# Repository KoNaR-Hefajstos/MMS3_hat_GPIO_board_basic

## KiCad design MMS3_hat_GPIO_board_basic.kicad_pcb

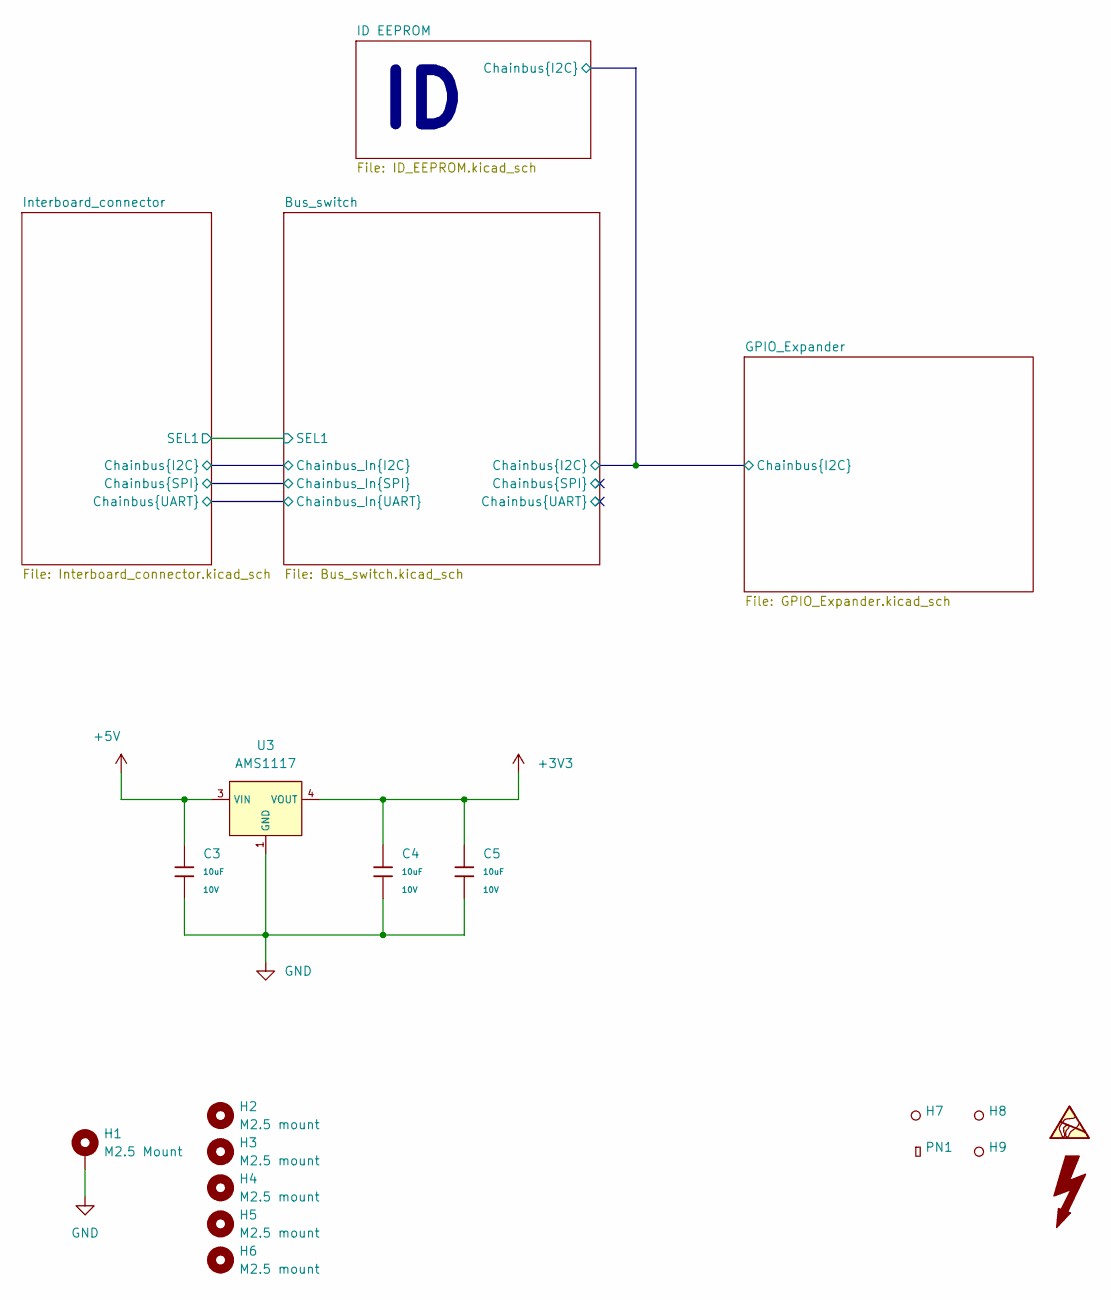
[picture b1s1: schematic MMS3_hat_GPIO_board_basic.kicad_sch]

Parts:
C3, C4, C5: 10uF; C_0603; Voltage Rated 10V; Tolerance ±10%; Part CL10A106KP8NNNC; LCSC C19702
H1: M2.5 Mount; MountingHole_2.7mm_M2.5_DIN965_Pad_TopOnly
H2, H3, H4, H5, H6: M2.5 mount; MountingHole_2.7mm_M2.5
H7, H8, H9: Hole_Tooling_JLCPCB
PN1: Part_Num_JLCPCB
U3: AMS1117; SOT-223-3_L6.5-W3.4-P2.30-LS7.0-BR; Output Voltage 3.3V; Dropout Voltage 1.3V@(800mA); Part AMS1117-3.3; LCSC C6186

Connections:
+3V3: C4.1, C5.1, U3.2 (VOUT), U3.4 (VOUT); also elsewhere on the board
+5V: C3.1, U3.3 (VIN); also elsewhere on the board
GND: C3.2, C4.2, C5.2, H1.1 (1_1), U3.1 (GND); also elsewhere on the board

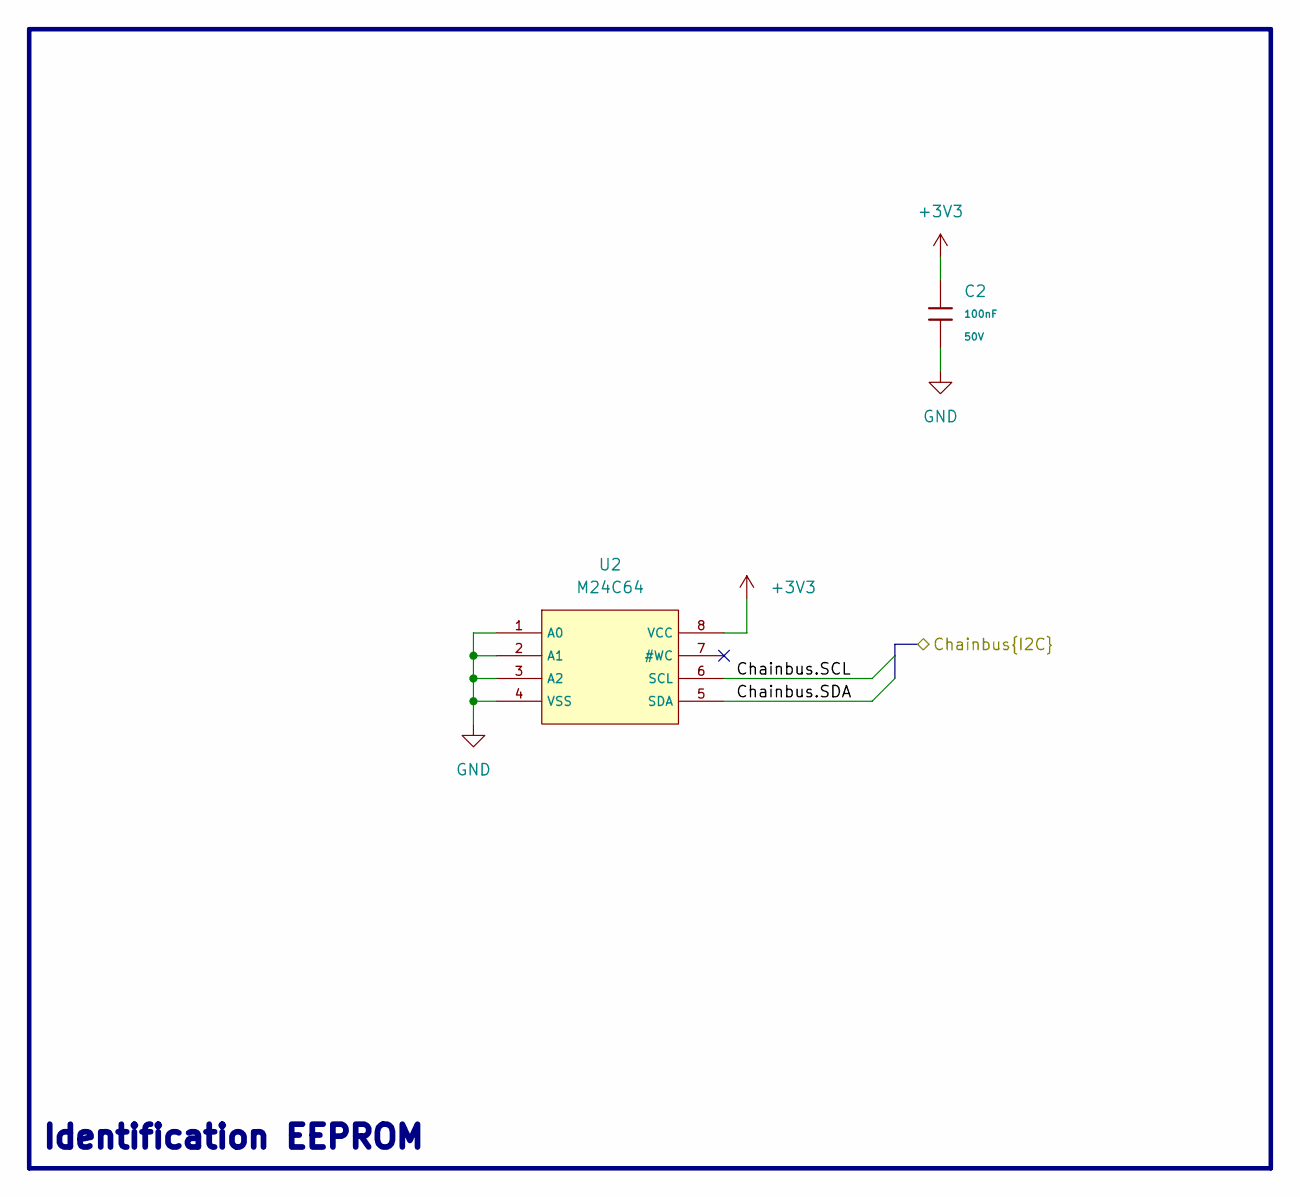
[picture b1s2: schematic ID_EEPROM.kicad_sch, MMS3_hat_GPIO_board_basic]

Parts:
C2: 100nF; C_0603; Voltage Rated 50V; Tolerance ±10%; Part CC0603KRX7R9BB104; LCSC C14663
U2: M24C64; SOIC-8_L5.0-W4.0-P1.27-LS6.0-BL; Supply Voltage 1.8V~5.5V; Part M24C64-RMN6TP; LCSC C79988

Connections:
+3V3: C2.1, U2.8 (VCC); also elsewhere on the board
/Bus_switch/Chainbus.SCL: U2.6 (SCL); also elsewhere on the board
/Bus_switch/Chainbus.SDA: U2.5 (SDA); also elsewhere on the board
GND: C2.2, U2.1 (A0), U2.2 (A1), U2.3 (A2), U2.4 (VSS); also elsewhere on the board

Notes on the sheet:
Identification EEPROM

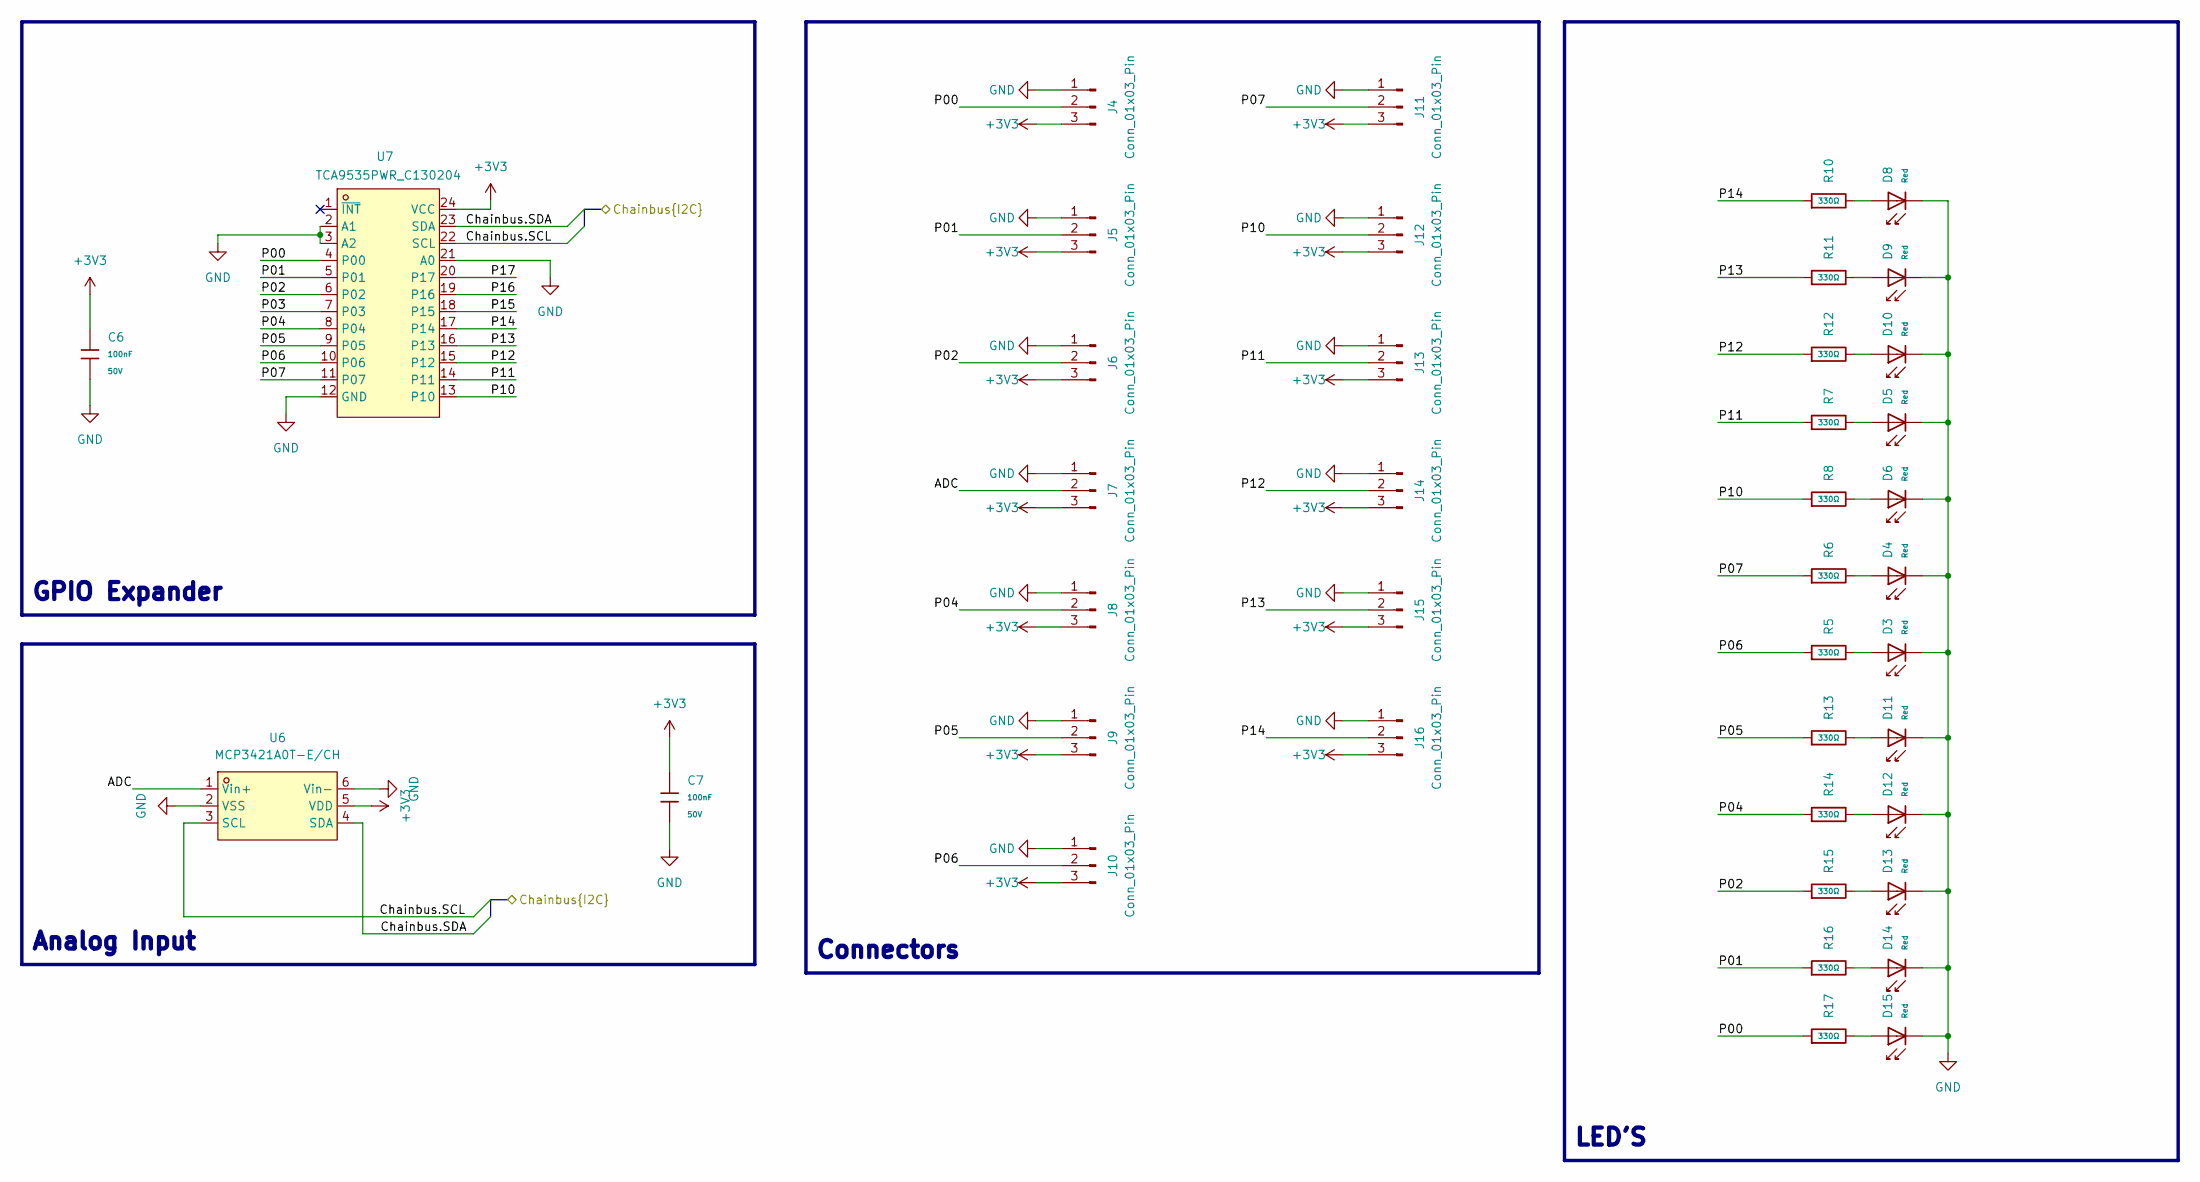
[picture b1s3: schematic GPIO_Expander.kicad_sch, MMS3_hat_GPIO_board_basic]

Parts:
C6, C7: 100nF; C_0603; Voltage Rated 50V; Tolerance ±10%; Part CC0603KRX7R9BB104; LCSC C14663
D3, D4, D5, D6, D8, D9, D10, D11, D12, D13, D14, D15: Red; D_0603; Part KT-0603R; LCSC C2286
J4, J5, J6, J7, J8, J9, J10, J11, J12, J13, J14, J15, J16: Conn_01x03_Pin; JST_XH_S3B-XH-A_1x03_P2.50mm_Horizontal
R5, R6, R7, R8, R10, R11, R12, R13, R14, R15, R16, R17: 330Ω; R_0402; Overload Voltage (Max) 50V; Tolerance ±1%; Part 0402WGF3300TCE; LCSC C25104
U6: MCP3421A0T-E/CH; SOT-23-6_L2.9-W1.6-P0.95-LS2.8-BR; MPN MCP3421A0T-E/CH; LCSC Part C29454
U7: TCA9535PWR_C130204; TSSOP-24_L7.8-W4.4-P0.65-LS6.4-BL; MPN TCA9535PWR; LCSC Part C130204

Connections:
+3V3: C6.1, C7.1, J4.3, J5.3, J6.3, J7.3, J8.3, J9.3, J10.3, J11.3, J12.3, J13.3, J14.3, J15.3, J16.3, U6.5 (VDD), U7.24 (VCC); also elsewhere on the board
/Bus_switch/Chainbus.SCL: U6.3 (SCL), U7.22 (SCL); also elsewhere on the board
/Bus_switch/Chainbus.SDA: U6.4 (SDA), U7.23 (SDA); also elsewhere on the board
/GPIO_Expander/ADC: J7.2, U6.1 (Vin+)
/GPIO_Expander/P00: J4.2, R17.1, U7.4 (P00)
/GPIO_Expander/P01: J5.2, R16.1, U7.5 (P01)
/GPIO_Expander/P02: J6.2, R15.1, U7.6 (P02)
/GPIO_Expander/P03: U7.7 (P03)
/GPIO_Expander/P04: J8.2, R14.1, U7.8 (P04)
/GPIO_Expander/P05: J9.2, R13.1, U7.9 (P05)
/GPIO_Expander/P06: J10.2, R5.1, U7.10 (P06)
/GPIO_Expander/P07: J11.2, R6.1, U7.11 (P07)
/GPIO_Expander/P10: J12.2, R8.1, U7.13 (P10)
/GPIO_Expander/P11: J13.2, R7.1, U7.14 (P11)
/GPIO_Expander/P12: J14.2, R12.1, U7.15 (P12)
/GPIO_Expander/P13: J15.2, R11.1, U7.16 (P13)
/GPIO_Expander/P14: J16.2, R10.1, U7.17 (P14)
/GPIO_Expander/P15: U7.18 (P15)
/GPIO_Expander/P16: U7.19 (P16)
/GPIO_Expander/P17: U7.20 (P17)
GND: C6.2, C7.2, D3.1, D4.1, D5.1, D6.1, D8.1, D9.1, D10.1, D11.1, D12.1, D13.1, D14.1, D15.1, J4.1, J5.1, J6.1, J7.1, J8.1, J9.1, J10.1, J11.1, J12.1, J13.1, J14.1, J15.1, J16.1, U6.2 (VSS), U6.6 (Vin-), U7.2 (A1), U7.3 (A2), U7.12 (GND), U7.21 (A0); also elsewhere on the board
unnamed: D3.2, R5.2
unnamed: D4.2, R6.2
unnamed: D5.2, R7.2
unnamed: D6.2, R8.2
unnamed: D8.2, R10.2
unnamed: D9.2, R11.2
unnamed: D10.2, R12.2
unnamed: D11.2, R13.2
unnamed: D12.2, R14.2
unnamed: D13.2, R15.2
unnamed: D14.2, R16.2
unnamed: D15.2, R17.2

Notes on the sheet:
GPIO Expander
LED'S
Connectors
Analog Input

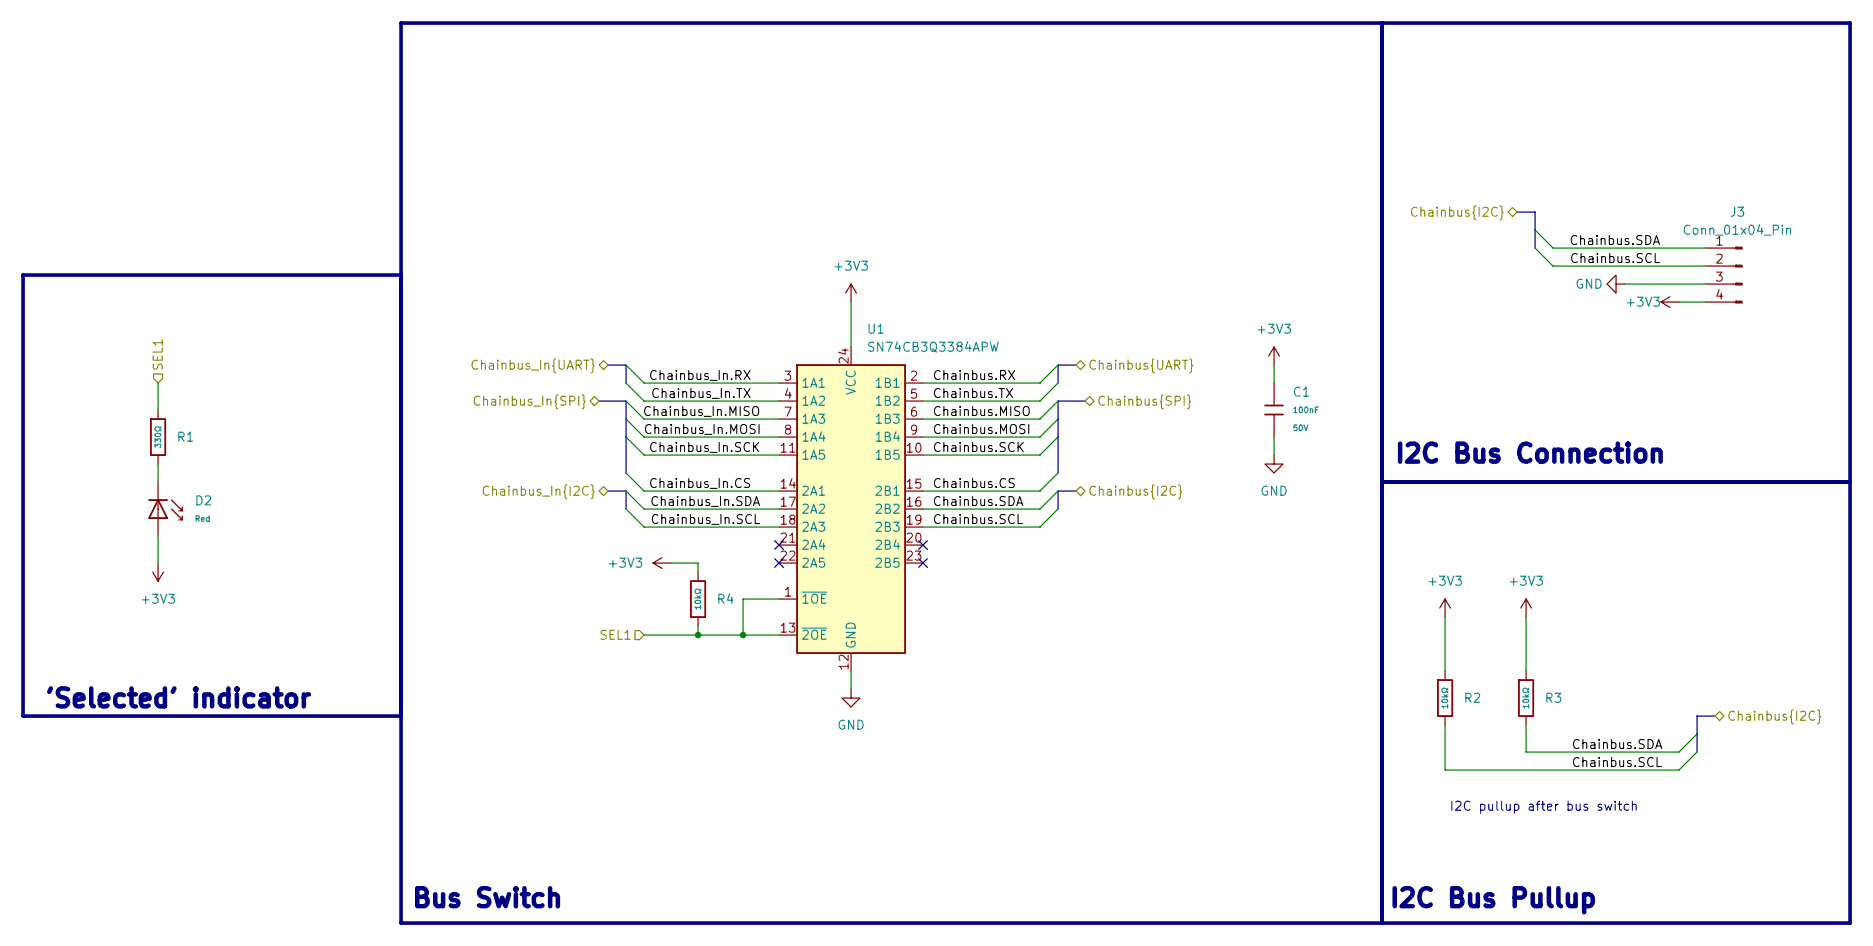
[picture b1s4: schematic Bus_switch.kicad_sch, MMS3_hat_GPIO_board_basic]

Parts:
C1: 100nF; C_0603; Voltage Rated 50V; Tolerance ±10%; Part CC0603KRX7R9BB104; LCSC C14663
D2: Red; D_0603; Part KT-0603R; LCSC C2286
J3: Conn_01x04_Pin; PinHeader_1x04_P2.54mm_Vertical
R1: 330Ω; R_0402; Overload Voltage (Max) 50V; Tolerance ±1%; Part 0402WGF3300TCE; LCSC C25104
R2, R3, R4: 10kΩ; R_0402; Overload Voltage (Max) 50V; Tolerance ±1%; Part 0402WGF1002TCE; LCSC C25744
U1: SN74CB3Q3384APW; TSSOP-24_4.4x7.8mm_P0.65mm; LCSC C469874

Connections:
+3V3: C1.1, D2.2, J3.4, R2.1, R3.1, R4.2, U1.24 (VCC); also elsewhere on the board
/Bus_switch/Chainbus.CS: U1.15 (2B1)
/Bus_switch/Chainbus.MISO: U1.6 (1B3)
/Bus_switch/Chainbus.MOSI: U1.9 (1B4)
/Bus_switch/Chainbus.RX: U1.2 (1B1)
/Bus_switch/Chainbus.SCK: U1.10 (1B5)
/Bus_switch/Chainbus.SCL: J3.2, R2.2, U1.19 (2B3); also elsewhere on the board
/Bus_switch/Chainbus.SDA: J3.1, R3.2, U1.16 (2B2); also elsewhere on the board
/Bus_switch/Chainbus.TX: U1.5 (1B2)
/Bus_switch/Chainbus_In.CS: U1.14 (2A1); also elsewhere on the board
/Bus_switch/Chainbus_In.MISO: U1.7 (1A3); also elsewhere on the board
/Bus_switch/Chainbus_In.MOSI: U1.8 (1A4); also elsewhere on the board
/Bus_switch/Chainbus_In.RX: U1.3 (1A1); also elsewhere on the board
/Bus_switch/Chainbus_In.SCK: U1.11 (1A5); also elsewhere on the board
/Bus_switch/Chainbus_In.SCL: U1.18 (2A3); also elsewhere on the board
/Bus_switch/Chainbus_In.SDA: U1.17 (2A2); also elsewhere on the board
/Bus_switch/Chainbus_In.TX: U1.4 (1A2); also elsewhere on the board
/Bus_switch/SEL1: R1.1, R4.1, U1.1 (~1OE), U1.13 (~2OE); also elsewhere on the board
GND: C1.2, J3.3, U1.12 (GND); also elsewhere on the board
unnamed: D2.1, R1.2

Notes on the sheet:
Bus Switch
'Selected' indicator
I2C Bus Pullup
I2C pullup after bus switch
I2C Bus Connection

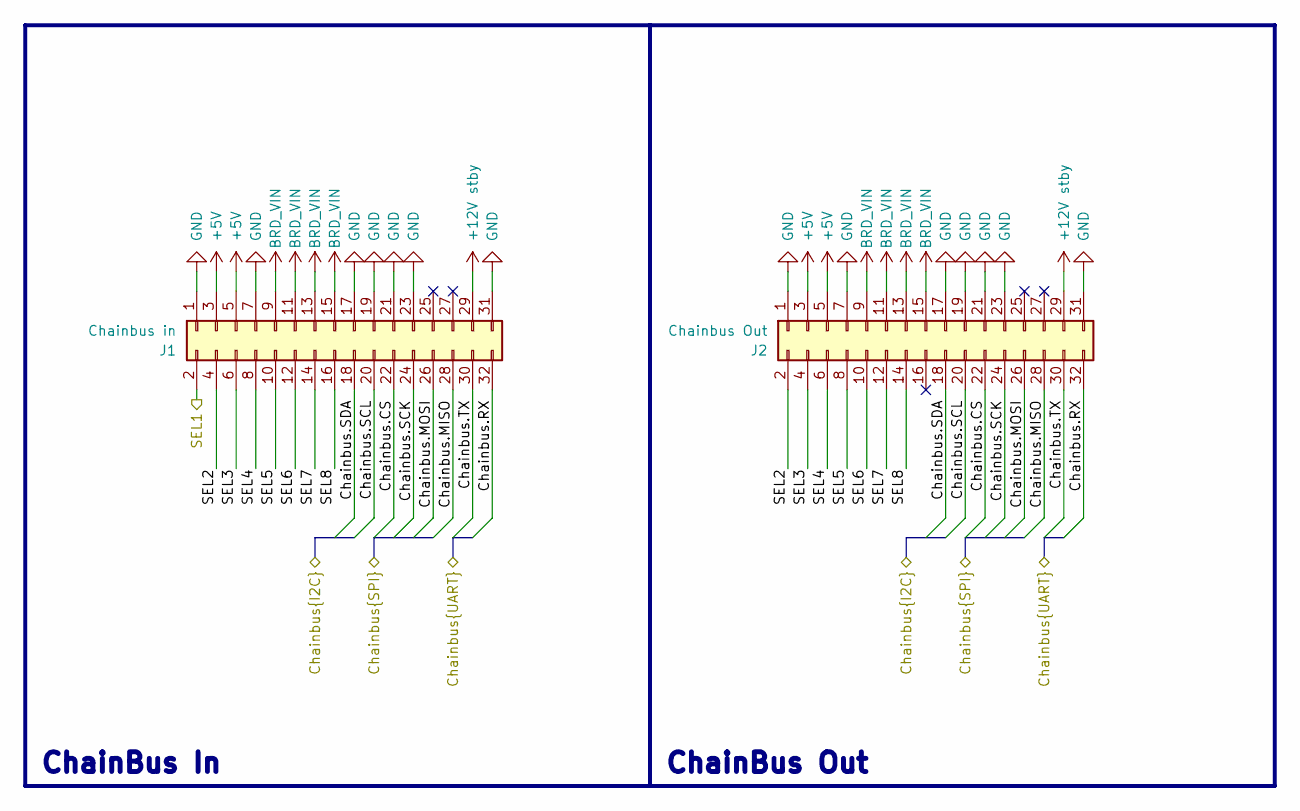
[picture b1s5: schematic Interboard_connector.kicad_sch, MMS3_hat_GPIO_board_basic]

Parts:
J1: Chainbus in; PinHeader_2x16_P2.54mm_Vertical_SMD
J2: Chainbus Out; PinSocket_2x16_P2.54mm_Vertical_SMD

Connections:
+5V: J1.3, J1.5, J2.3, J2.5; also elsewhere on the board
+12V stby: J1.29, J2.29
/Bus_switch/Chainbus_In.CS: J1.22, J2.22; also elsewhere on the board
/Bus_switch/Chainbus_In.MISO: J1.28, J2.28; also elsewhere on the board
/Bus_switch/Chainbus_In.MOSI: J1.26, J2.26; also elsewhere on the board
/Bus_switch/Chainbus_In.RX: J1.32, J2.32; also elsewhere on the board
/Bus_switch/Chainbus_In.SCK: J1.24, J2.24; also elsewhere on the board
/Bus_switch/Chainbus_In.SCL: J1.20, J2.20; also elsewhere on the board
/Bus_switch/Chainbus_In.SDA: J1.18, J2.18; also elsewhere on the board
/Bus_switch/Chainbus_In.TX: J1.30, J2.30; also elsewhere on the board
/Bus_switch/SEL1: J1.2; also elsewhere on the board
/Interboard_connector/SEL2: J1.4, J2.2
/Interboard_connector/SEL3: J1.6, J2.4
/Interboard_connector/SEL4: J1.8, J2.6
/Interboard_connector/SEL5: J1.10, J2.8
/Interboard_connector/SEL6: J1.12, J2.10
/Interboard_connector/SEL7: J1.14, J2.12
/Interboard_connector/SEL8: J1.16, J2.14
BRD_VIN: J1.9, J1.11, J1.13, J1.15, J2.9, J2.11, J2.13, J2.15
GND: J1.1, J1.7, J1.17, J1.19, J1.21, J1.23, J1.31, J2.1, J2.7, J2.17, J2.19, J2.21, J2.23, J2.31; also elsewhere on the board

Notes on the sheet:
ChainBus In
ChainBus Out

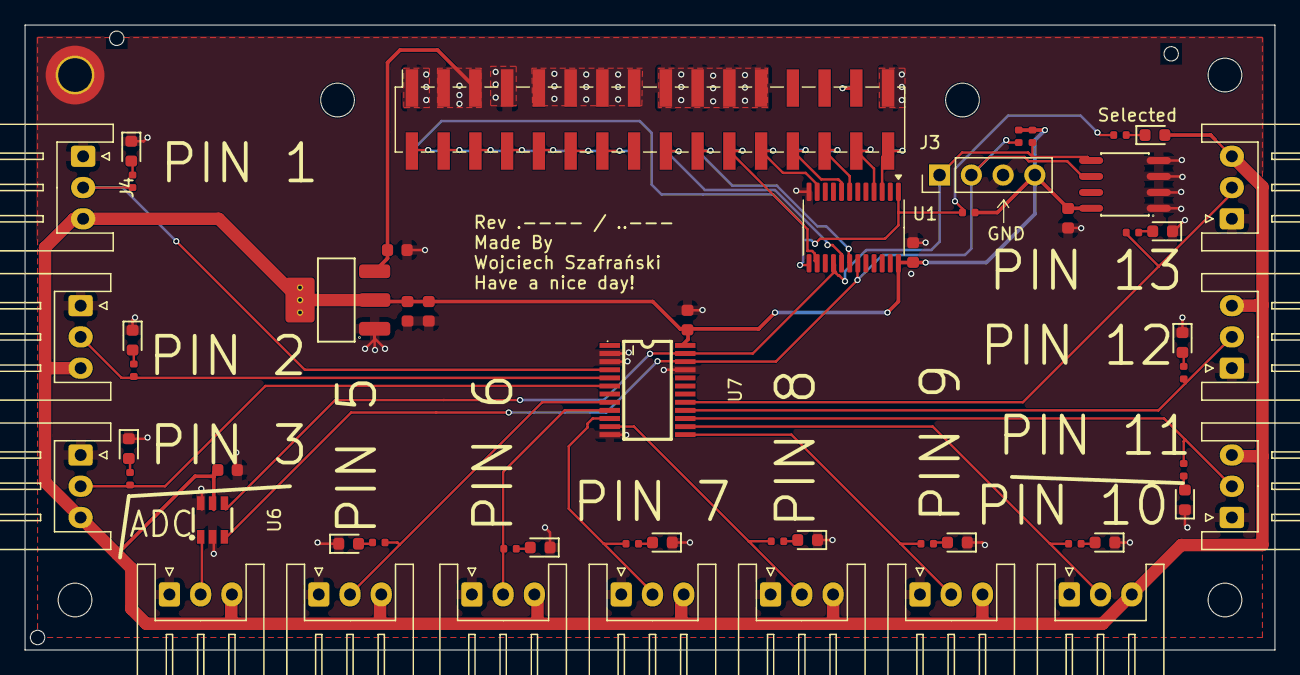
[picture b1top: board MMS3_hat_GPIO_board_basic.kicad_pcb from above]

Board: 2 copper layers, 100.0 x 50.0 mm, 66 parts (1 on the bottom side), 49 nets.

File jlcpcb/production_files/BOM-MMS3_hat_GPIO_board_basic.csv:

Comment,Designator,Footprint,LCSC,Quantity
100nF,"C1,C2,C6,C7",C_0603,C14663,4
10kΩ,"R2,R3,R4",R_0402,C25744,3
10uF,"C3,C4,C5",C_0603,C19702,3
330Ω,"R1,R10,R11,R12,R13,R14,R15,R16,R17,R5,R6,R7,R8",R_0402,C25104,13
AMS1117,U3,SOT-223-3_L6.5-W3.4-P2.30-LS7.0-BR,C6186,1
M24C64,U2,SOIC-8_L5.0-W4.0-P1.27-LS6.0-BL,C79988,1
MCP3421A0T-E/CH,U6,SOT-23-6_L2.9-W1.6-P0.95-LS2.8-BR,C29454,1
Red,"D10,D11,D12,D13,D14,D15,D2,D3,D4,D5,D6,D8,D9",D_0603,C2286,13
SN74CB3Q3384APW,U1,TSSOP-24_4.4x7.8mm_P0.65mm,C469874,1
TCA9535PWR_C130204,U7,TSSOP-24_L7.8-W4.4-P0.65-LS6.4-BL,C130204,1

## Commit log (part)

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2026-03-01 cleaned up the repo
2026-03-01 added routing and gerber
2026-03-01 added adc
2026-03-12 cosmetic changes
2026-04-17 added leds and bom. Revison 1.2
2026-04-18 fixed selected led polarity
2026-04-20 generated final gerber
